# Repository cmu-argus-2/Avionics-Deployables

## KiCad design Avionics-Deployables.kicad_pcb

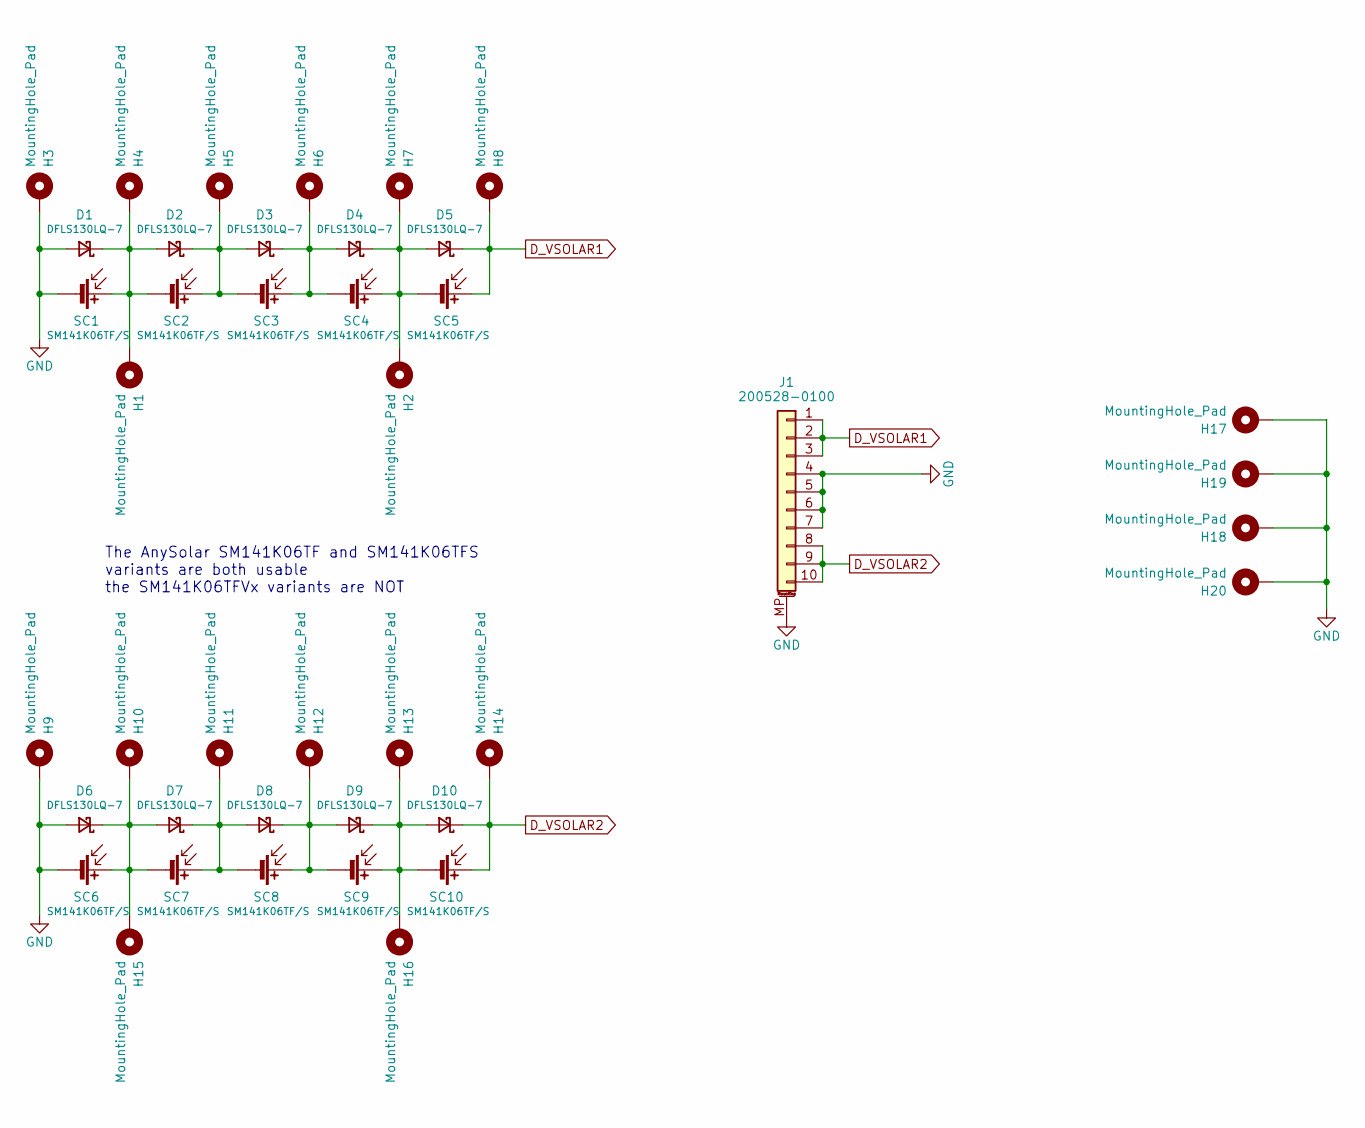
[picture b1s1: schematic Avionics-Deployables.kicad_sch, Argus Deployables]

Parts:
D1, D2, D3, D4, D5, D6, D7, D8, D9, D10: DFLS130LQ-7; D_PowerDI-123
H1, H2, H3, H4, H5, H6, H7, H8, H9, H10, H11, H12, H13, H14, H15, H16, H17, H18, H19, H20: MountingHole_Pad; TestPoint_Pad_D1.0mm
J1: 200528-0100; Molex_200528-0100_1x10-1MP_P1.00mm_Horizontal
SC1, SC2, SC3, SC4, SC5, SC6, SC7, SC8, SC9, SC10: SM141K06TF/S; SM141K06TF_S

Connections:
D_VSOLAR1: D5.1 (K), H8.1, J1.1, J1.2, J1.3, SC5.1 (+)
D_VSOLAR2: D10.1 (K), H14.1, J1.8, J1.9, J1.10, SC10.1 (+)
GND: D1.2 (A), D6.2 (A), H3.1, H9.1, H17.1, H18.1, H19.1, H20.1, J1.4, J1.5, J1.6, J1.7, J1.MP (MountPin), SC1.2 (-), SC6.2 (-)
unnamed: D1.1 (K), D2.2 (A), H1.1, H4.1, SC1.1 (+), SC2.2 (-)
unnamed: D2.1 (K), D3.2 (A), H5.1, SC2.1 (+), SC3.2 (-)
unnamed: D3.1 (K), D4.2 (A), H6.1, SC3.1 (+), SC4.2 (-)
unnamed: D4.1 (K), D5.2 (A), H2.1, H7.1, SC4.1 (+), SC5.2 (-)
unnamed: D6.1 (K), D7.2 (A), H10.1, H15.1, SC6.1 (+), SC7.2 (-)
unnamed: D7.1 (K), D8.2 (A), H11.1, SC7.1 (+), SC8.2 (-)
unnamed: D8.1 (K), D9.2 (A), H12.1, SC8.1 (+), SC9.2 (-)
unnamed: D9.1 (K), D10.2 (A), H13.1, H16.1, SC9.1 (+), SC10.2 (-)

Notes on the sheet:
The AnySolar SM141K06TF and SM141K06TFS variants are both usable the SM141K06TFVx variants are NOT

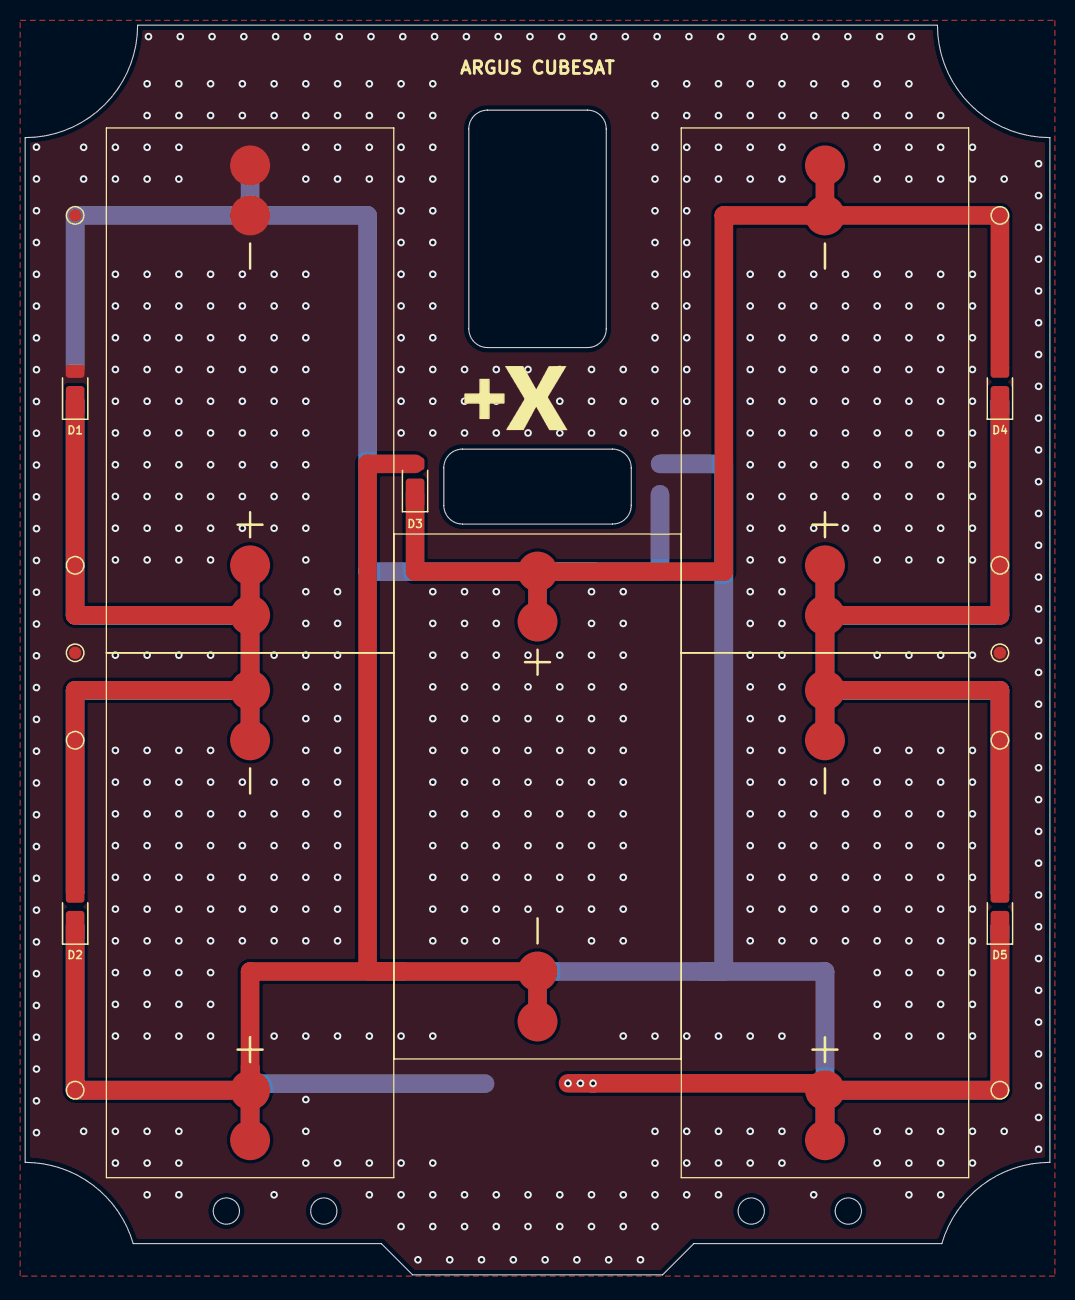
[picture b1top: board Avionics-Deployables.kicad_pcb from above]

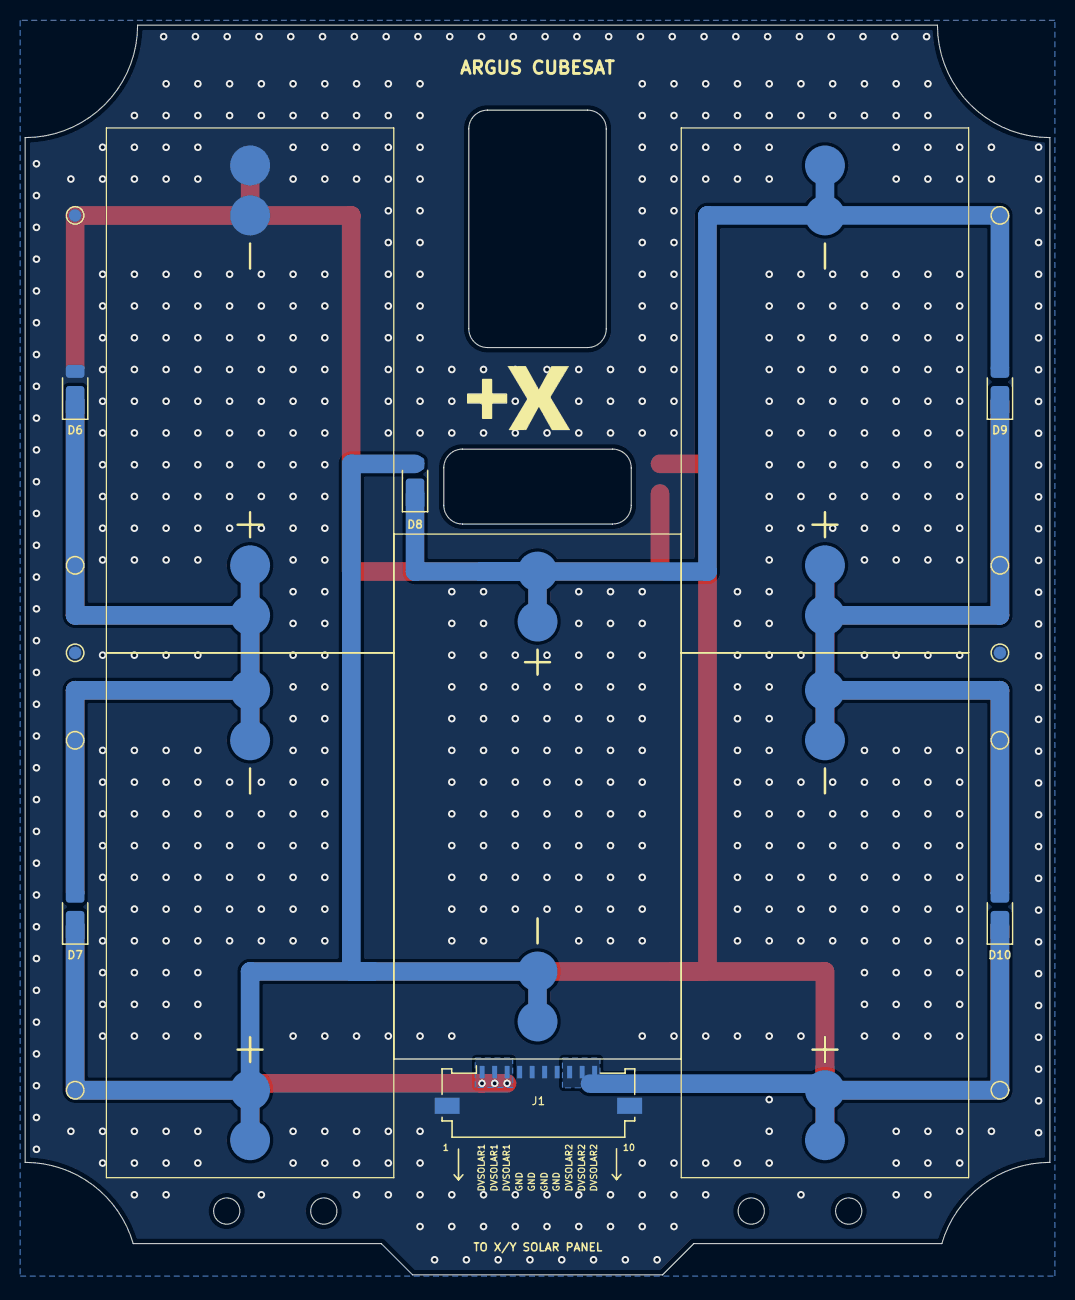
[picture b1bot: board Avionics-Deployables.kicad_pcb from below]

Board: 2 copper layers, 82.0 x 100.0 mm, 43 parts (22 on the bottom side), 11 nets.

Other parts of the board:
Ref**: Val**; ypanel
Ref**#2: Val**; ypanel

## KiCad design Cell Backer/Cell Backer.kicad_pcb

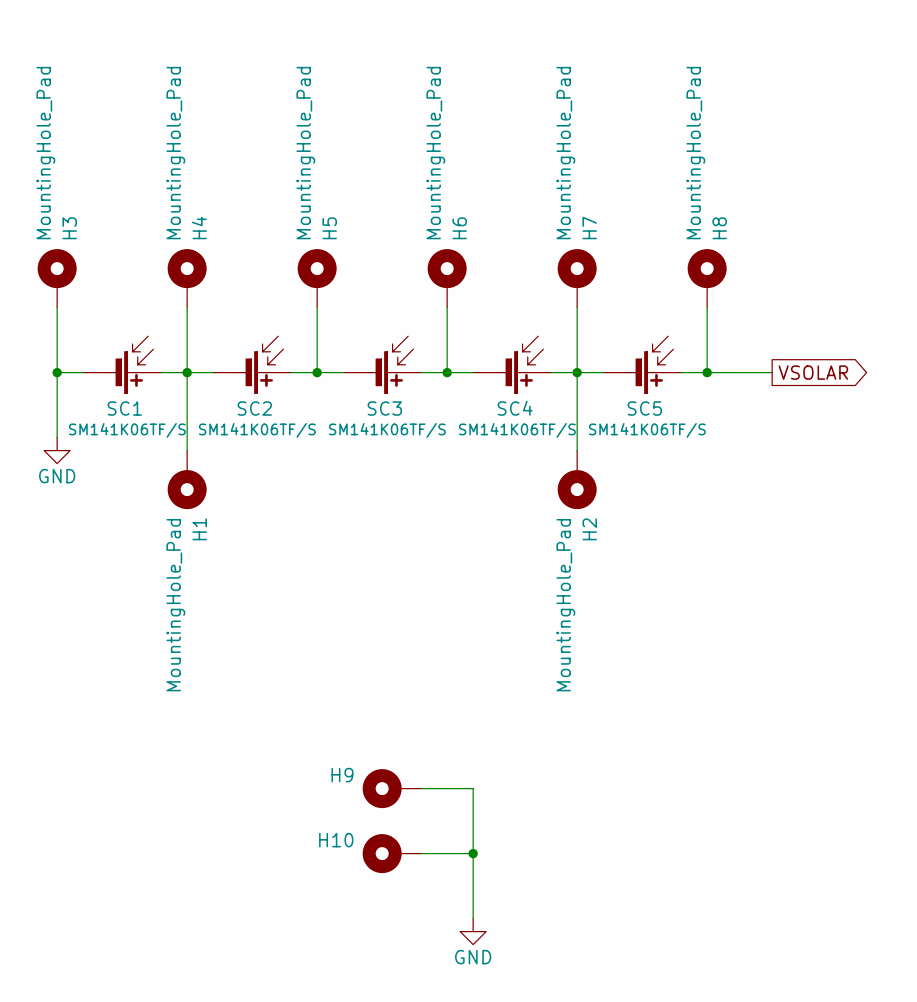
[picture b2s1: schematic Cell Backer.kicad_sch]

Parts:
H1, H2, H3, H4, H5, H6, H7, H8, H9, H10: MountingHole_Pad; MountingHole_1mm
SC1, SC2, SC3, SC4, SC5: SM141K06TF/S; SM141K06TF_S

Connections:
GND: H3.1, H9.1, H10.1, SC1.2 (-)
unnamed: H1.1, H4.1, SC1.1 (+), SC2.2 (-)
unnamed: H5.1, SC2.1 (+), SC3.2 (-)
unnamed: H6.1, SC3.1 (+), SC4.2 (-)
unnamed: H2.1, H7.1, SC4.1 (+), SC5.2 (-)
VSOLAR: H8.1, SC5.1 (+)

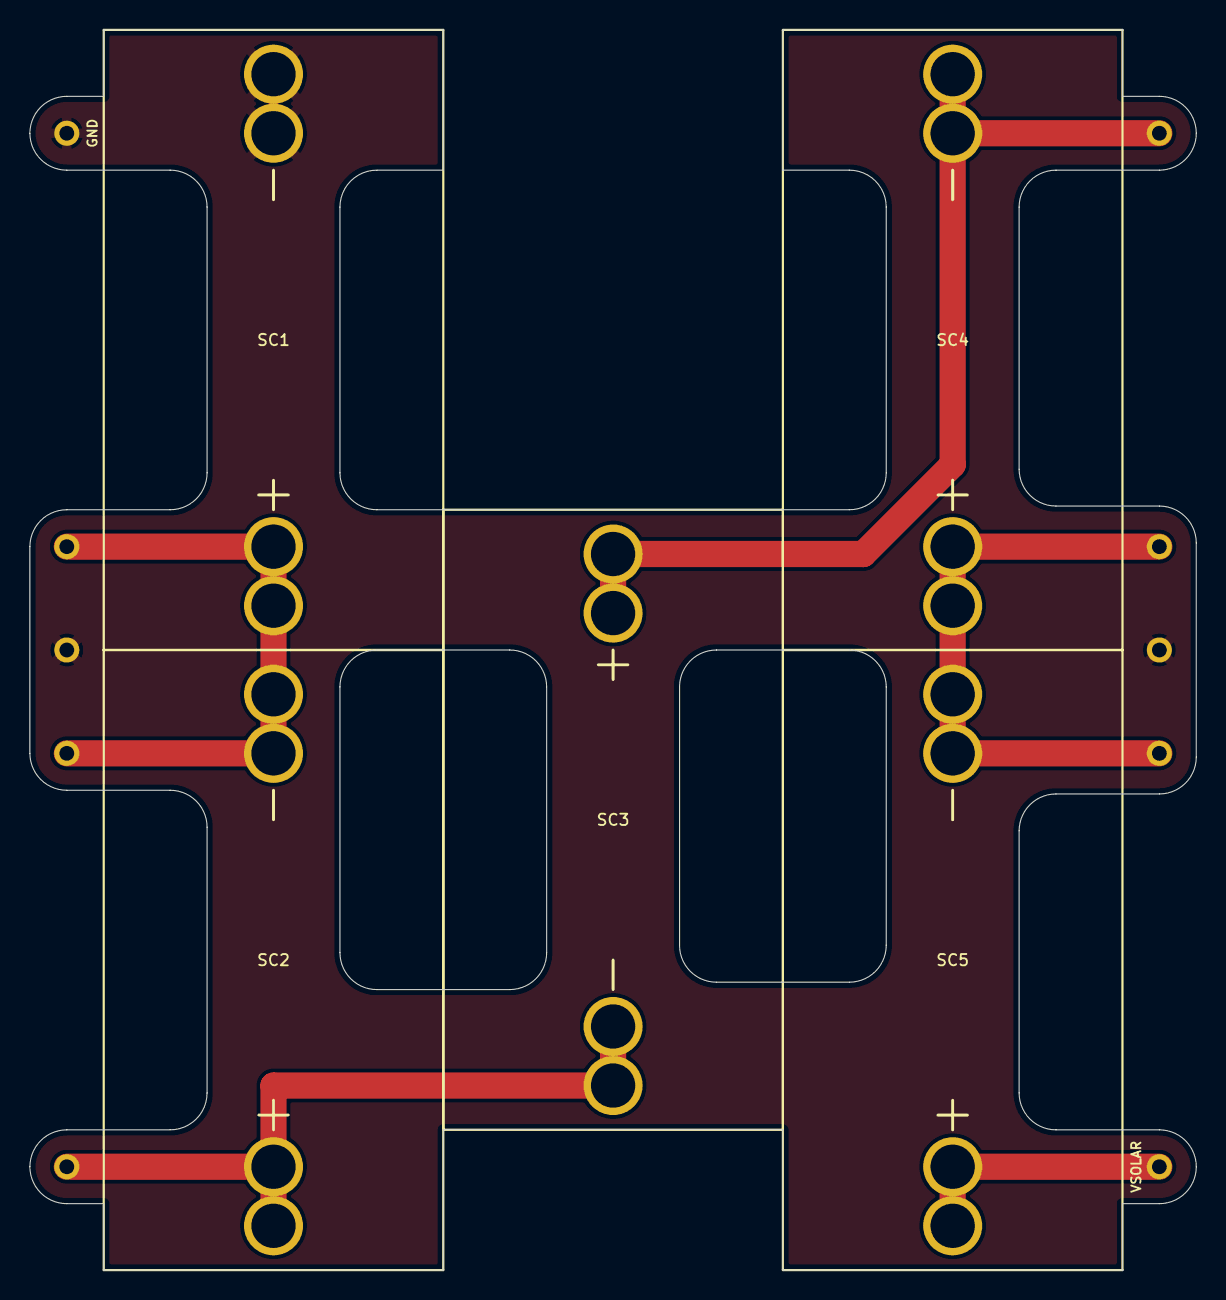
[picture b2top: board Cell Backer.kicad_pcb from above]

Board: 2 copper layers, 79.0 x 84.0 mm, 15 parts (0 on the bottom side), 6 nets.

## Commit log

2024-06-10 Upload .gitignore
2024-07-02 Files upload
2024-10-22 Export BOM
2024-11-19 Update Deployable outlines
2025-04-12 Update solar cell footprints
2025-04-12 Exported BOM and STEP files
2025-06-19 v2.3 Updates
2026-02-09 V3 Updates and Cell Backer
